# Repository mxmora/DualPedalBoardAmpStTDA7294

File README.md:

# DualPedalBoardAmpStTDA7294
DualPedalBoardAmpStTDA7294

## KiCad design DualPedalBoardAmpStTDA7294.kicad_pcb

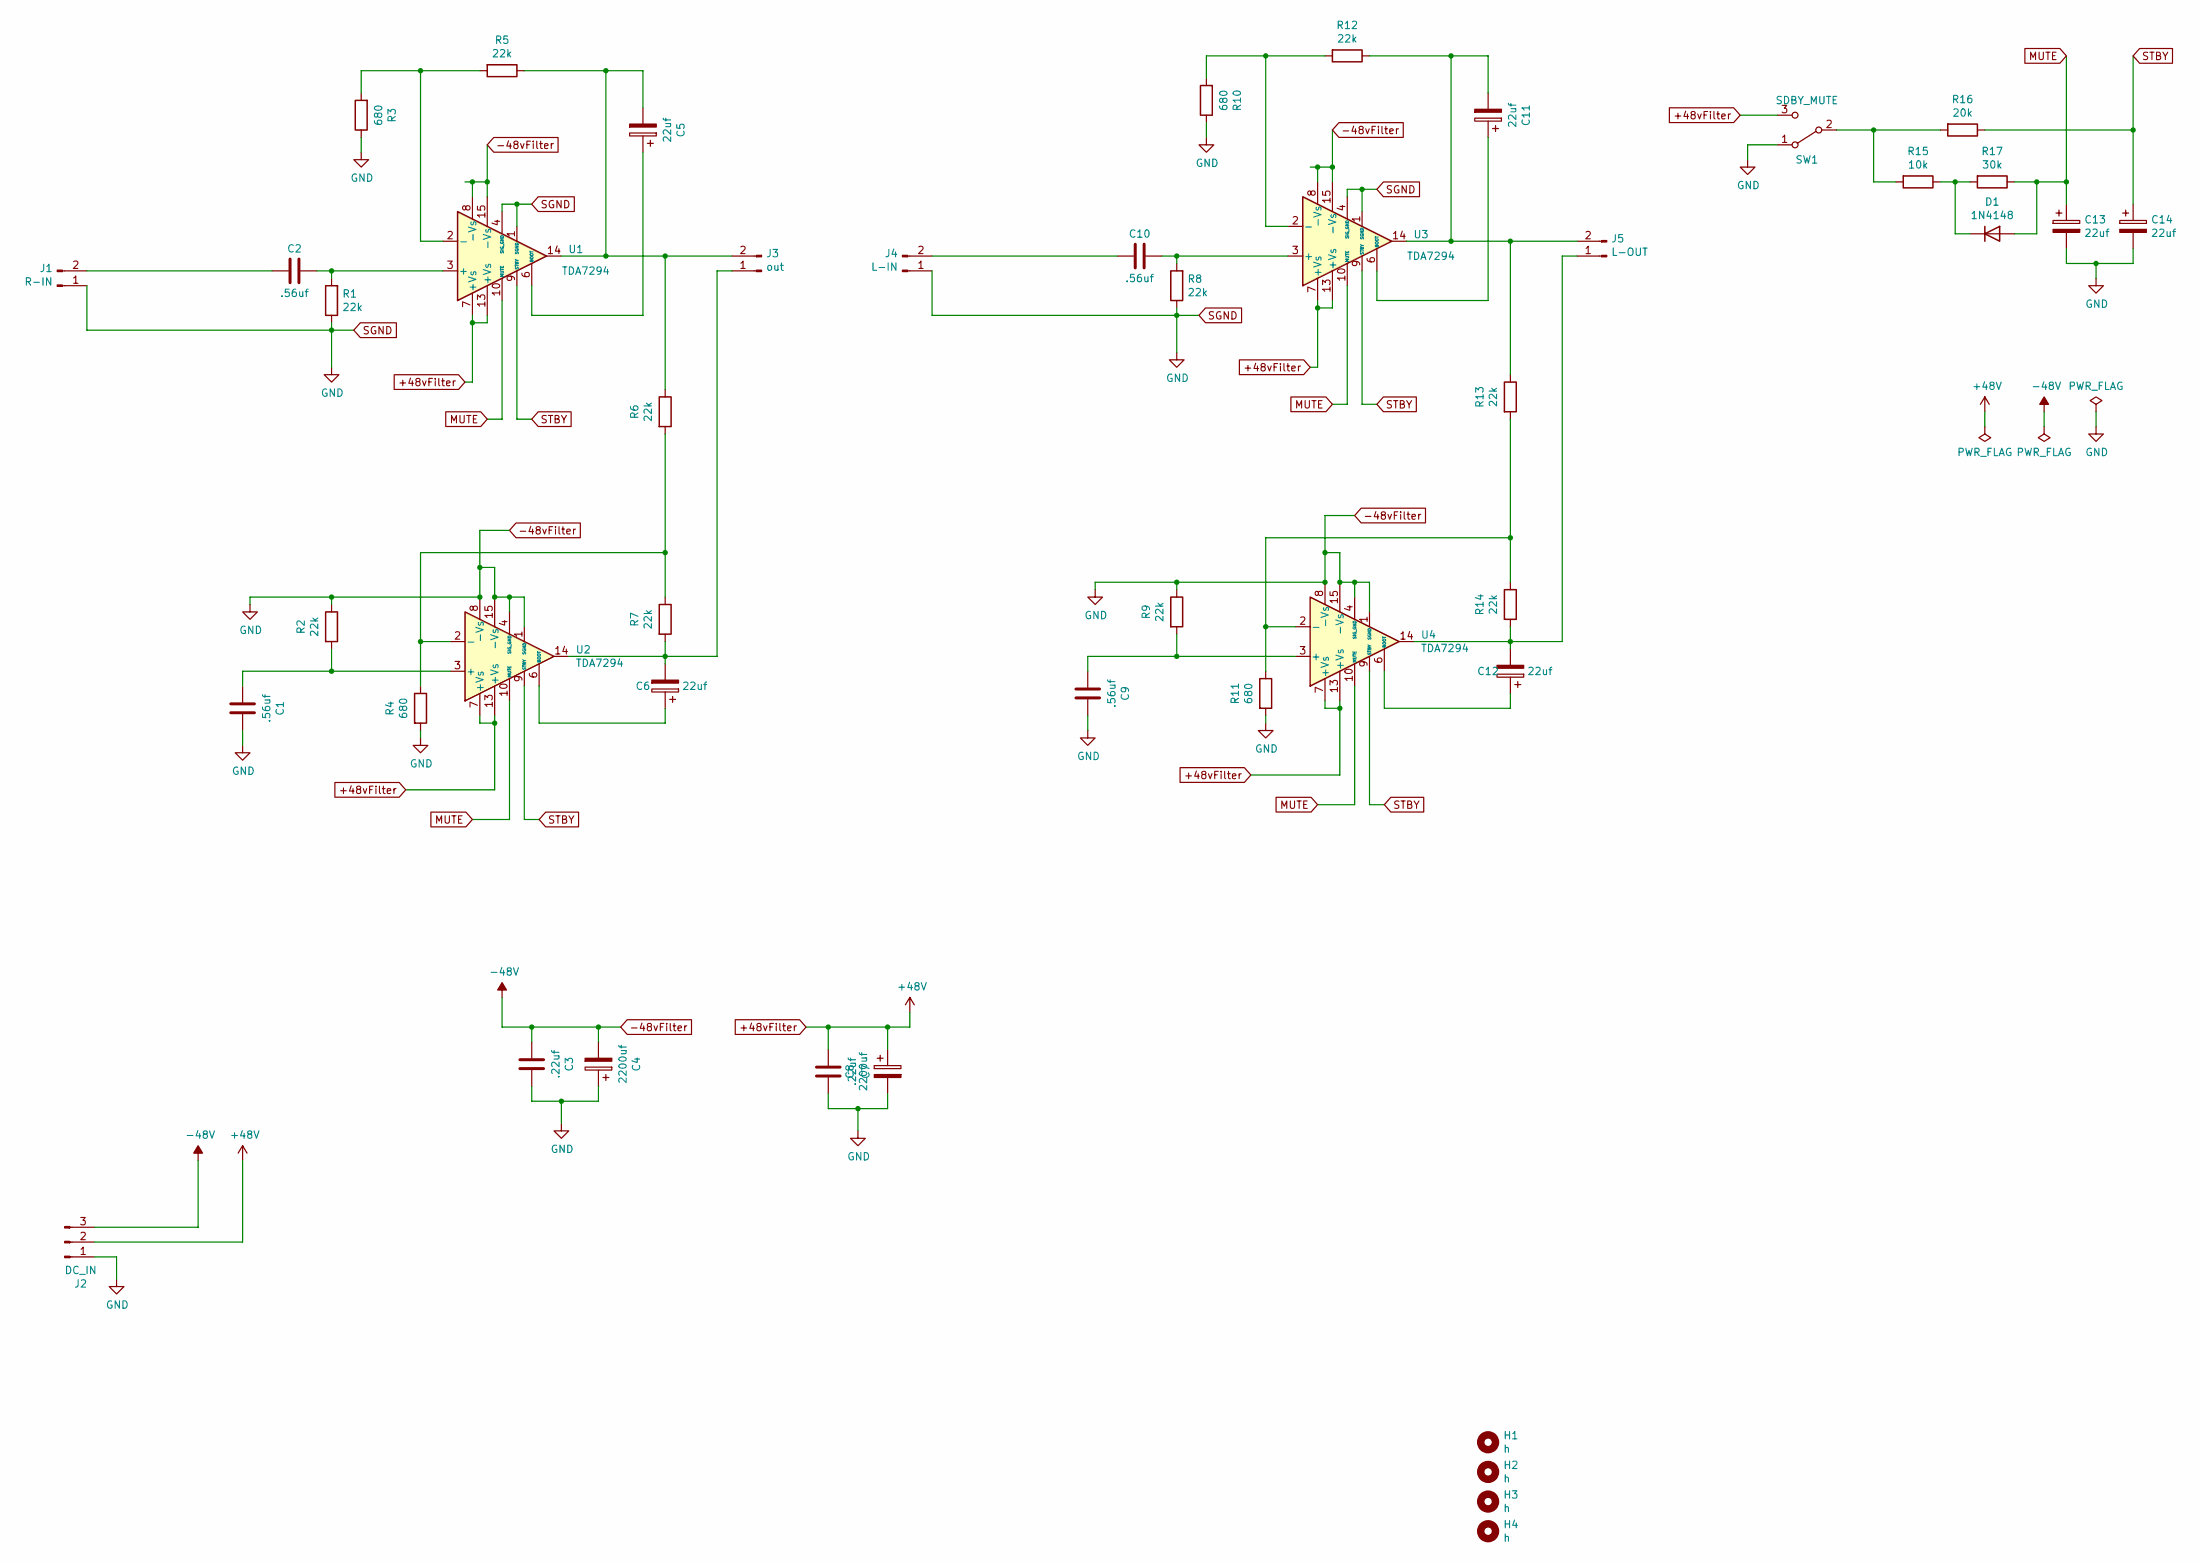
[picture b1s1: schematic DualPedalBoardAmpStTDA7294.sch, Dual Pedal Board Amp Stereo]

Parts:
C1, C2, C9, C10: .56uf; C_Rect_L7.0mm_W3.5mm_P5.00mm
C3, C7: .22uf; C_Rect_L7.0mm_W3.5mm_P5.00mm
C4, C8: 2200uf; CP_Radial_D16.0mm_P7.50mm
C5, C6, C11, C12, C13, C14: 22uf; CP_Radial_D8.0mm_P3.50mm
D1: 1N4148; D_DO-35_SOD27_P7.62mm_Horizontal
H1, H2, H3, H4: h; MountingHole_3.2mm_M3
J1: R-IN; PinHeader_1x02_P2.54mm_Vertical
J2: DC_IN; TerminalBlock_Phoenix_PT-1,5-4-3.5-H_1x04_P3.50mm_Horizontal
J3: out; PinHeader_1x02_P2.54mm_Vertical
J4: L-IN; PinHeader_1x02_P2.54mm_Vertical
J5: L-OUT; PinHeader_1x02_P2.54mm_Vertical
R1, R2, R5, R6, R7, R8, R9, R12, R13, R14: 22k; R_Axial_DIN0207_L6.3mm_D2.5mm_P10.16mm_Horizontal
R3, R4, R10, R11: 680; R_Axial_DIN0207_L6.3mm_D2.5mm_P10.16mm_Horizontal
R15: 10k; R_Axial_DIN0207_L6.3mm_D2.5mm_P10.16mm_Horizontal
R16: 20k; R_Axial_DIN0207_L6.3mm_D2.5mm_P10.16mm_Horizontal
R17: 30k; R_Axial_DIN0207_L6.3mm_D2.5mm_P10.16mm_Horizontal
SW1: SDBY_MUTE; PinHeader_1x03_P2.54mm_Vertical
U1, U2, U3, U4: TDA7294; TO-220-15_P2.54x2.54mm_StaggerOdd_Lead4.58mm_Vertical

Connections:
+48vFilter: C7.2, C8.1, J2.2, SW1.3 (C), U1.7 (+Vs), U1.13 (+Vs), U2.7 (+Vs), U2.13 (+Vs), U3.7 (+Vs), U3.13 (+Vs), U4.7 (+Vs), U4.13 (+Vs)
-48vFilter: C1.1, C3.1, C3.2, C4.1, C4.2, C7.1, C8.2, C9.1, C13.2, C14.2, J1.1, J2.1, J2.3, J4.1, R1.1, R2.1, R3.1, R4.2, R8.1, R9.1, R10.1, R11.2, SW1.1 (A), U1.1 (SGND), U1.4 (SIG_GND), U1.8 (-Vs), U1.15 (-Vs), U2.1 (SGND), U2.4 (SIG_GND), U2.8 (-Vs), U2.15 (-Vs), U3.1 (SGND), U3.4 (SIG_GND), U3.8 (-Vs), U3.15 (-Vs), U4.1 (SGND), U4.4 (SIG_GND), U4.8 (-Vs), U4.15 (-Vs)
MUTE: C13.1, D1.2 (A), R17.1, U1.10 (MUTE), U2.10 (MUTE), U3.10 (MUTE), U4.10 (MUTE)
unnamed: C1.2, R2.2, U2.3 (+)
unnamed: C2.1, R1.2, U1.3 (+)
unnamed: C2.2, J1.2
unnamed: C5.1, U1.6 (BOOT)
unnamed: C5.2, J3.2, R5.1, R6.1, U1.14
unnamed: C6.1, U2.6 (BOOT)
unnamed: C6.2, J3.1, R7.2, U2.14
unnamed: C9.2, R9.2, U4.3 (+)
unnamed 11: C10.1, R8.2, U3.3 (+); also elsewhere on the board
unnamed: C10.2, J4.2
unnamed 13: C11.1, U3.6 (BOOT); also elsewhere on the board
unnamed: C11.2, J5.2, R12.1, R13.1, U3.14
unnamed: C12.1, U4.6 (BOOT)
unnamed: C12.2, J5.1, R14.2, U4.14
unnamed: D1.1 (K), R15.1, R17.2
unnamed: R3.2, R5.2, U1.2 (-)
unnamed: R4.1, R6.2, R7.1, U2.2 (-)
unnamed: R10.2, R12.2, U3.2 (-)
unnamed: R11.1, R13.2, R14.1, U4.2 (-)
unnamed: R15.2, R16.2, SW1.2 (B)
STBY: C14.1, R16.1, U1.9 (STBY), U2.9 (STBY), U3.9 (STBY), U4.9 (STBY)

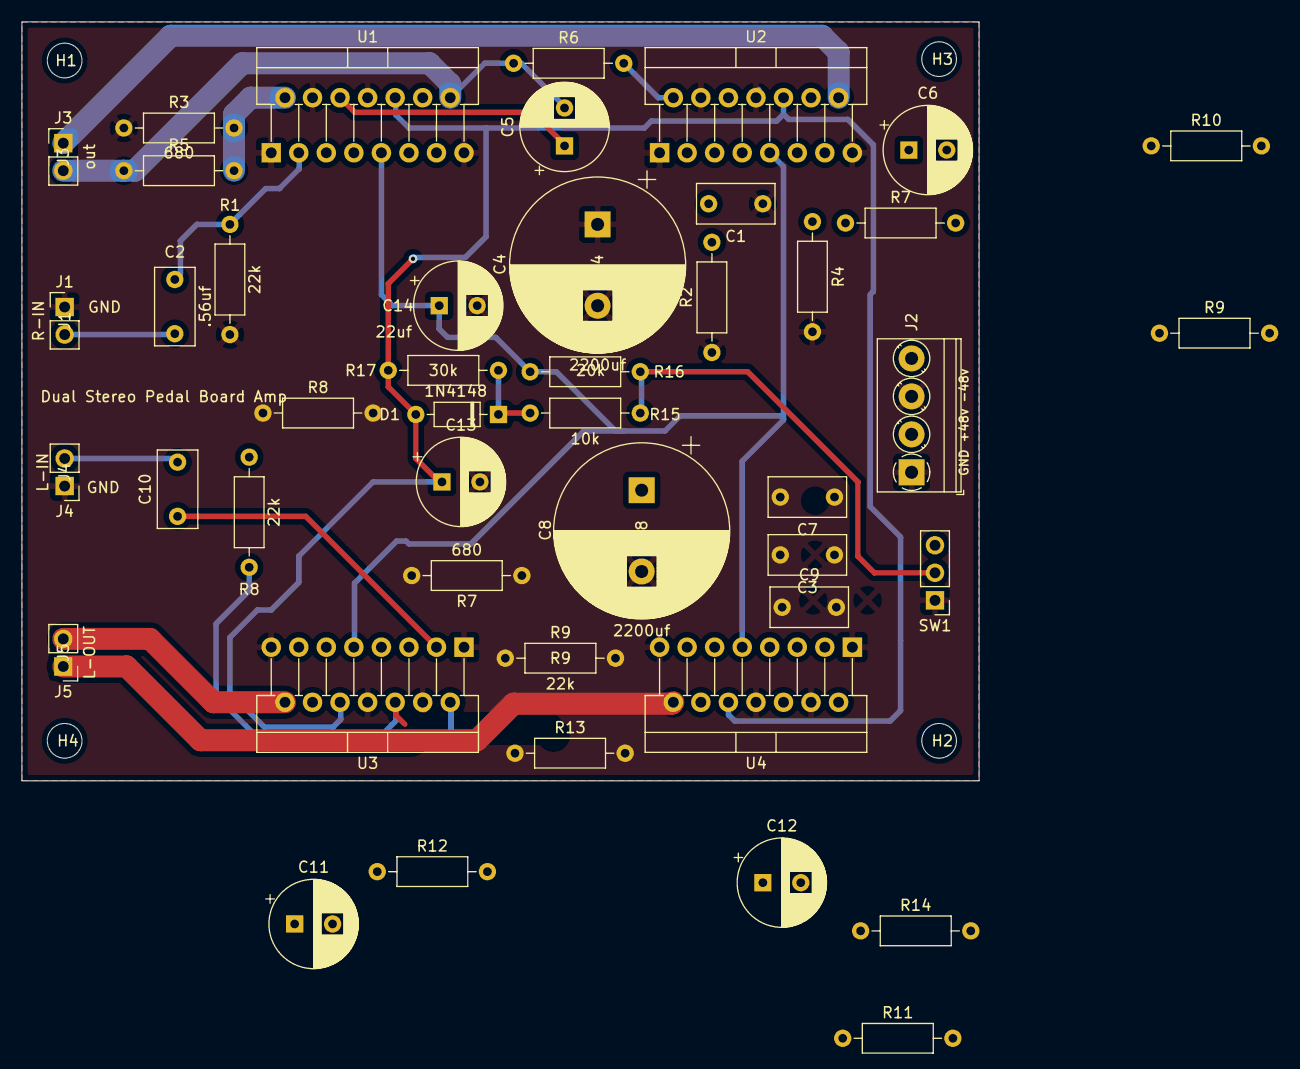
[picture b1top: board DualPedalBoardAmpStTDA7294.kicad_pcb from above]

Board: 4 copper layers, 88.3 x 70.0 mm, 49 parts (0 on the bottom side), 25 nets.

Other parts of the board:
R7#2: 680; R_Axial_DIN0207_L6.3mm_D2.5mm_P10.16mm_Horizontal
R8#2, R9#2: 22k; R_Axial_DIN0207_L6.3mm_D2.5mm_P10.16mm_Horizontal

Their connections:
unnamed 11: R7#2.2; also elsewhere on the board
unnamed 13: R8#2.2; also elsewhere on the board
unnamed: R7#2.1, R9#2.2

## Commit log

2021-01-05 first check in
